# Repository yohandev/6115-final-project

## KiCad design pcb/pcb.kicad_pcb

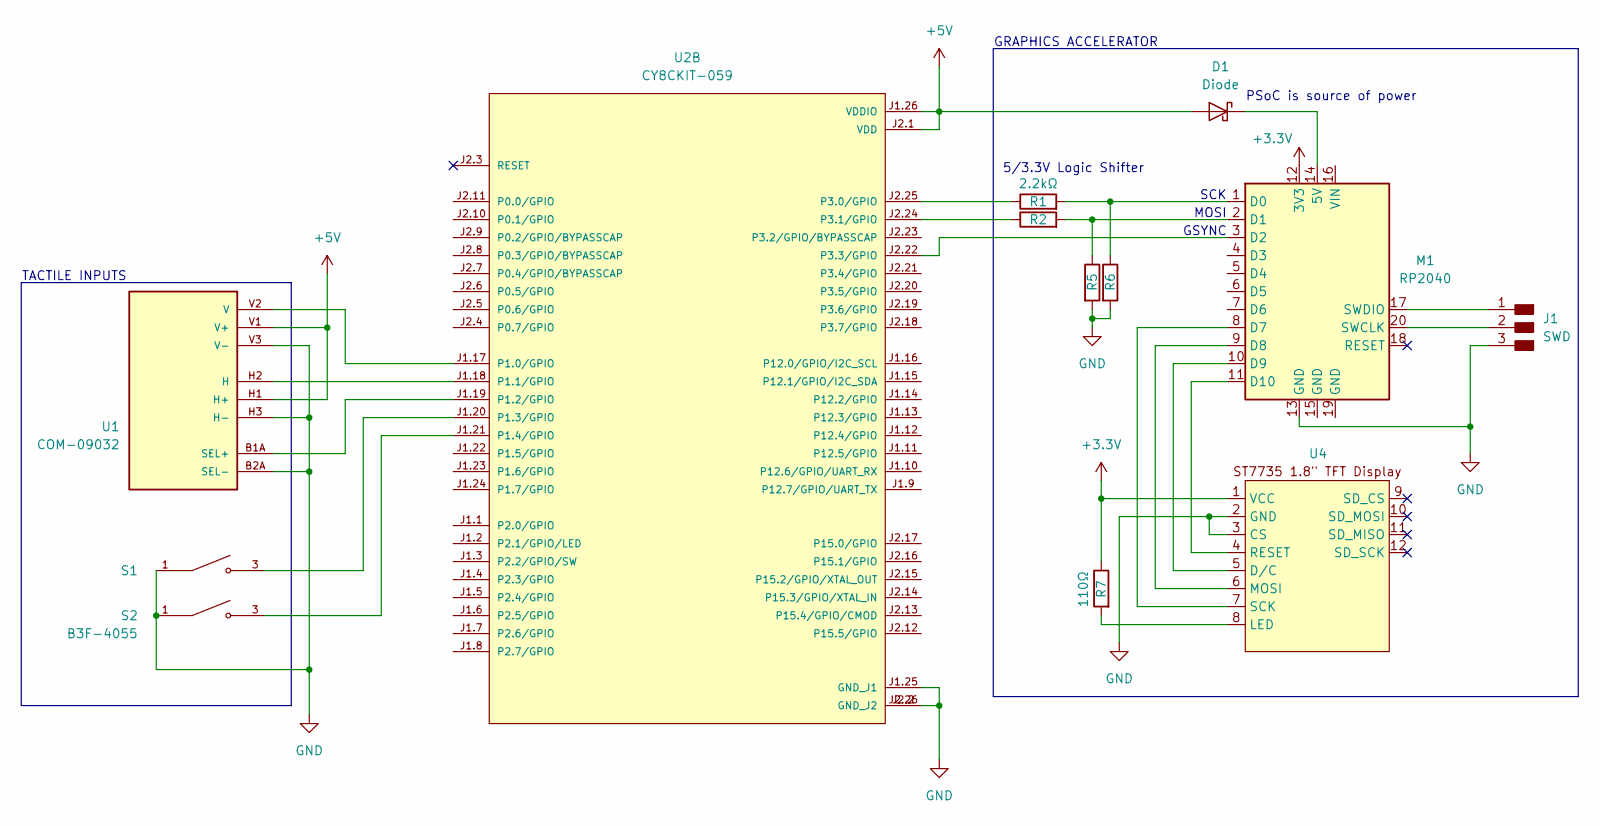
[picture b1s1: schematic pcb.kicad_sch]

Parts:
D1: Diode; SOD-123
J1: SWD; PinHeader_1x03_P2.54mm_Vertical_THT_D1mm
M1: RP2040; SeeedStudio_XIAO_RP2040
R1, R2: 2.2kΩ; R_1206_3216Metric
R5, R6: 3.3kΩ; R_1206_3216Metric
R7: 110Ω; R_1206_3216Metric
S1, S2: B3F-4055; SW_B3F-4055; PARTREV A070-E1-08
U1: COM-09032; XDCR_COM-09032; PARTREV N/A
U2: CY8CKIT-059; MODULE_CY8CKIT-059; PARTREV G
U4: ST7735

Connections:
+3.3V: M1.12 (3V3), R7.1, U4.1 (VCC)
+5V: D1.2 (A), U1.H1 (H+), U1.V1 (V+), U2.J1.26 (VDDIO), U2.J2.1 (VDD)
GND: J1.3, M1.13 (GND), R5.2, R6.2, S1.1, S2.1, U1.B2A (SEL-), U1.H3 (H-), U1.V3 (V-), U2.J1.25 (GND_J1), U2.J2.2 (GND_J2), U2.J2.26 (GND_J2), U4.2 (GND), U4.3 (CS)
unnamed: D1.1 (K), M1.14 (5V)
unnamed: J1.1, M1.17 (SWDIO)
unnamed: J1.2, M1.20 (SWCLK)
unnamed: M1.1 (D0), R1.2, R6.1
unnamed: M1.2 (D1), R2.2, R5.1
unnamed: M1.3 (D2), U2.J2.22 (P3.3/GPIO)
unnamed: M1.8 (D7), U4.7 (SCK)
unnamed: M1.9 (D8), U4.6 (MOSI)
unnamed: M1.10 (D9), U4.5 (D/C)
unnamed: M1.11 (D10), U4.4 (RESET)
unnamed: U1.H2 (H), U2.J1.18 (P1.1/GPIO)
unnamed: U1.B1A (SEL+), U2.J1.19 (P1.2/GPIO)
unnamed: U1.V2 (V), U2.J1.17 (P1.0/GPIO)
unnamed: S1.3, U2.J1.20 (P1.3/GPIO)
unnamed: S2.3, U2.J1.21 (P1.4/GPIO)
unnamed: R1.1, U2.J2.25 (P3.0/GPIO)
unnamed: R2.1, U2.J2.24 (P3.1/GPIO)
unnamed: R7.2, U4.8 (LED)

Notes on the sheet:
GRAPHICS ACCELERATOR
MOSI
5/3.3V Logic Shifter
GSYNC
SCK
TACTILE INPUTS
PSoC is source of power

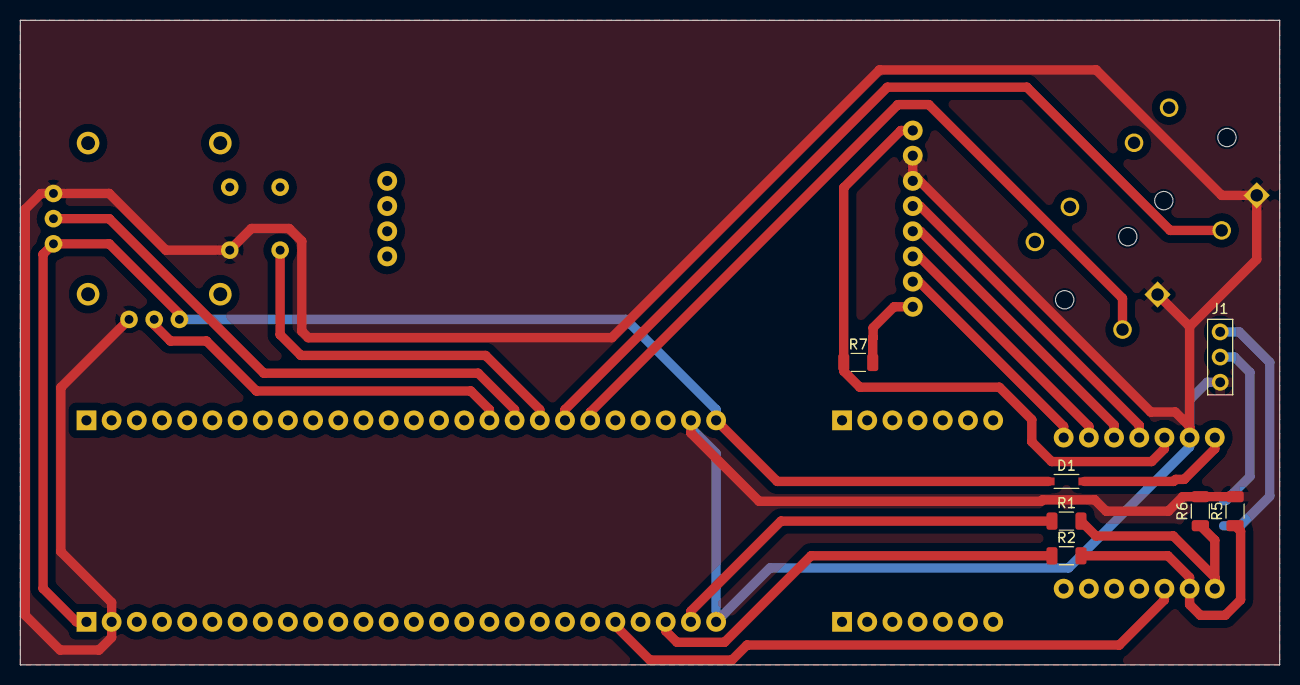
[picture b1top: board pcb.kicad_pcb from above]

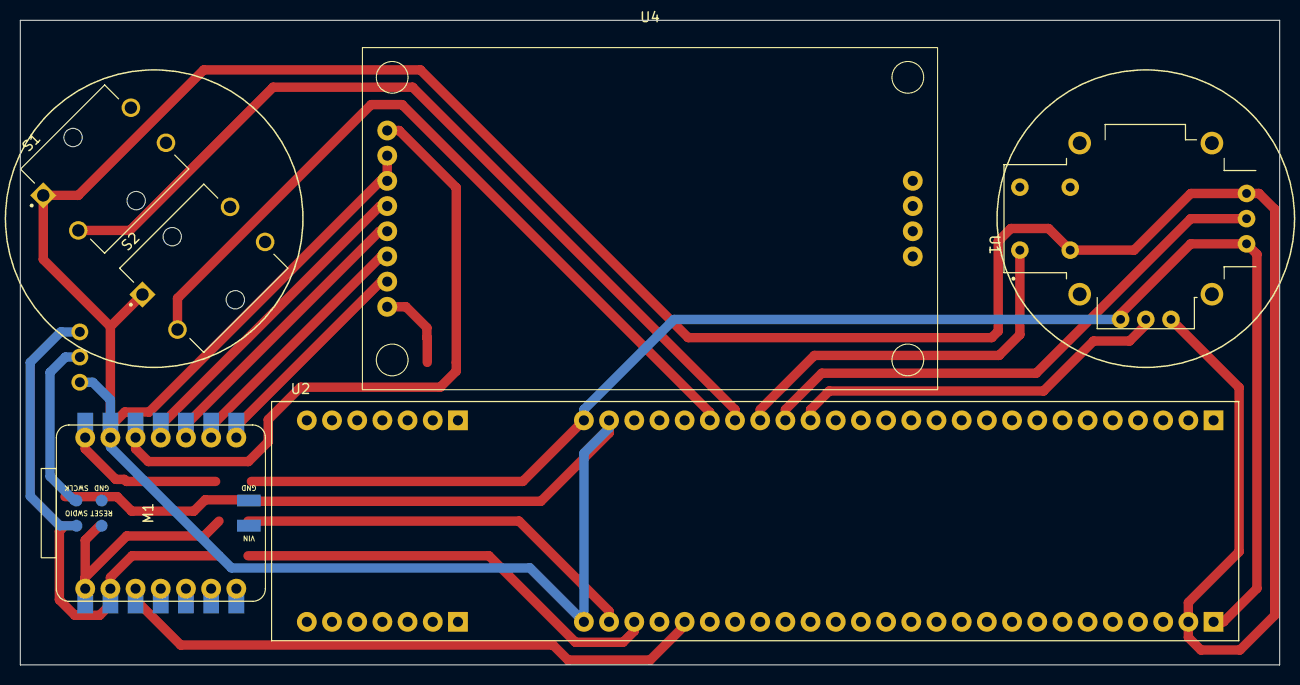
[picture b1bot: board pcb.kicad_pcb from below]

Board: 2 copper layers, 127.0 x 65.0 mm, 13 parts (6 on the bottom side), 21 nets.

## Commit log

2024-04-23 Add project proposal first draft
2024-04-23 Add initial proposal schematic
2024-04-23 Add project PCB
2024-04-23 Proposal revision
2024-04-24 Added the PSoC 5 + VS Code Template
2024-04-25 Added single ADC to joystick for testing
2024-04-25 Added UART over ProgKit
2024-04-25 Removed old PSoC project and initialized new one
2024-04-25 Added potentiometer + UART test
2024-04-25 Added joystick + buttons hardware and firmware
2024-04-25 Add type utilities
2024-04-25 Add PCB STEP file
2024-04-25 Add linear algebra utilities
2024-04-25 Setup the writeup document
2024-04-25 Add PCB casing files
2024-04-25 Rename to `num.h`
2024-04-26 Add asteroids
2024-04-26 Change `num.h` to add constants
2024-04-26 Add GPU skeleton code
2024-04-26 Serial monitor config for Visual Studio Code
2024-04-26 Fix compiler errors and change to
2024-04-26 GPU over serial implementation, client side
2024-04-26 Add a throttle for now
2024-04-27 Add mesh file generation
2024-04-27 Fix renaming errors
2024-04-27 Fixed pointer-type warnings
2024-04-29 Implement 3D viewer and packet parsing from serial
2024-04-29 Mesh unpacking on host side
2024-04-29 Wait for serial to be ready
2024-04-29 changes to workspace?
2024-04-29 Small fixes for UART communications
2024-04-29 builds idk
2024-04-29 Fix mesh upload errors, PSoC side
2024-04-29 Fix mesh upload errors, host side
2024-04-29 Remove dead code
2024-04-29 Rename asteroids to world
2024-04-30 Setup world for adding more stuff and rendering, etc.
2024-04-30 Added quaternion math
2024-04-30 Add X-Wing asset, rescale Star Destroyer asset
2024-04-30 Back to two columns
2024-04-30 Add X-wing asset
2024-04-30 Normalize joystick inputs
2024-04-30 Add basic player movement
2024-04-30 Add draw instanced (quaternion version)
2024-05-01 Switch to `trimesh` renderer
2024-05-01 Change scene
2024-05-01 comment out stuff not added yet
2024-05-01 Change fields in mesh to const
2024-05-01 Fix mesh file generation
2024-05-01 resolve all warnings
2024-05-01 add time/dt tracking
2024-05-01 increase baudrate
2024-05-01 Fix quaternion math for y-up coordinate system
2024-05-01 remove pragma once
2024-05-01 fixed coordinate system math
2024-05-02 Remove stale code
2024-05-02 Add quaternion slerp
2024-05-02 Remove wrong inline qualifiers
2024-05-02 better player controller w/ e.g. banking
2024-05-02 Add `vec3_lerp`
2024-05-02 Change default window size to fit
2024-05-02 Change meshes to right handed coordinate system
2024-05-02 Update quaternions to right handed coordinate
2024-05-02 Nvm, it was good
2024-05-02 Trying again, using GLM's implementation
2024-05-02 working camera follow, PSoC side
2024-05-02 Working camera follow, host side
2024-05-02 Add quaternion `angle_axis`
2024-05-02 Try alternative player movement model
2024-05-02 Add asteroids rendering
2024-05-02 Update asteroid world gen
2024-05-07 Setup SDK for Pi Pico
2024-05-07 Add build task using `probe-rs`
2024-05-07 Add RTT
2024-05-07 Moved `num.h` to `common/num.h`
2024-05-07 Add common code to RP2040 CMake project
2024-05-07 Add and modify `ST7789` driver from Pico examples
2024-05-08 Add DMA to LCD drivers
2024-05-08 Add framebuffer struct
2024-05-09 Add (very) naive triangle rasterizer
2024-05-09 Add triangle benchmark
2024-05-09 Add fixed point
2024-05-09 Add naive fixed point
2024-05-09 Smarter rasterizer algorithm
2024-05-09 Better indexing in rasterization impl
2024-05-09 Rename `vec3` --> `vec3f`
2024-05-09 Add fixed-point `vec3` type
2024-05-09 Add 8.8 fixed-point type
2024-05-09 Moved `Mesh` to `common/`
2024-05-09 Change rasterizer to 100% fixed point
2024-05-10 Ladies and gentlemen, we have monke on screen
2024-05-10 Add `vec3s` and `mat4` types
2024-05-14 Add `mat4f` transformations
2024-05-14 Monke on the screen!
2024-05-14 Back face culling and near clip plane
2024-05-14 Added lambert lighting
2024-05-14 Bouncing monke
2024-05-14 i forgot lol
2024-05-14 remove extra num.h
2024-05-14 fix compile errors
2024-05-14 Add SPI component
2024-05-14 Add RP2040 GPU impl
2024-05-14 flip SPI pins
2024-05-14 Add SPI input using PIO
2024-05-14 Write up WIP
